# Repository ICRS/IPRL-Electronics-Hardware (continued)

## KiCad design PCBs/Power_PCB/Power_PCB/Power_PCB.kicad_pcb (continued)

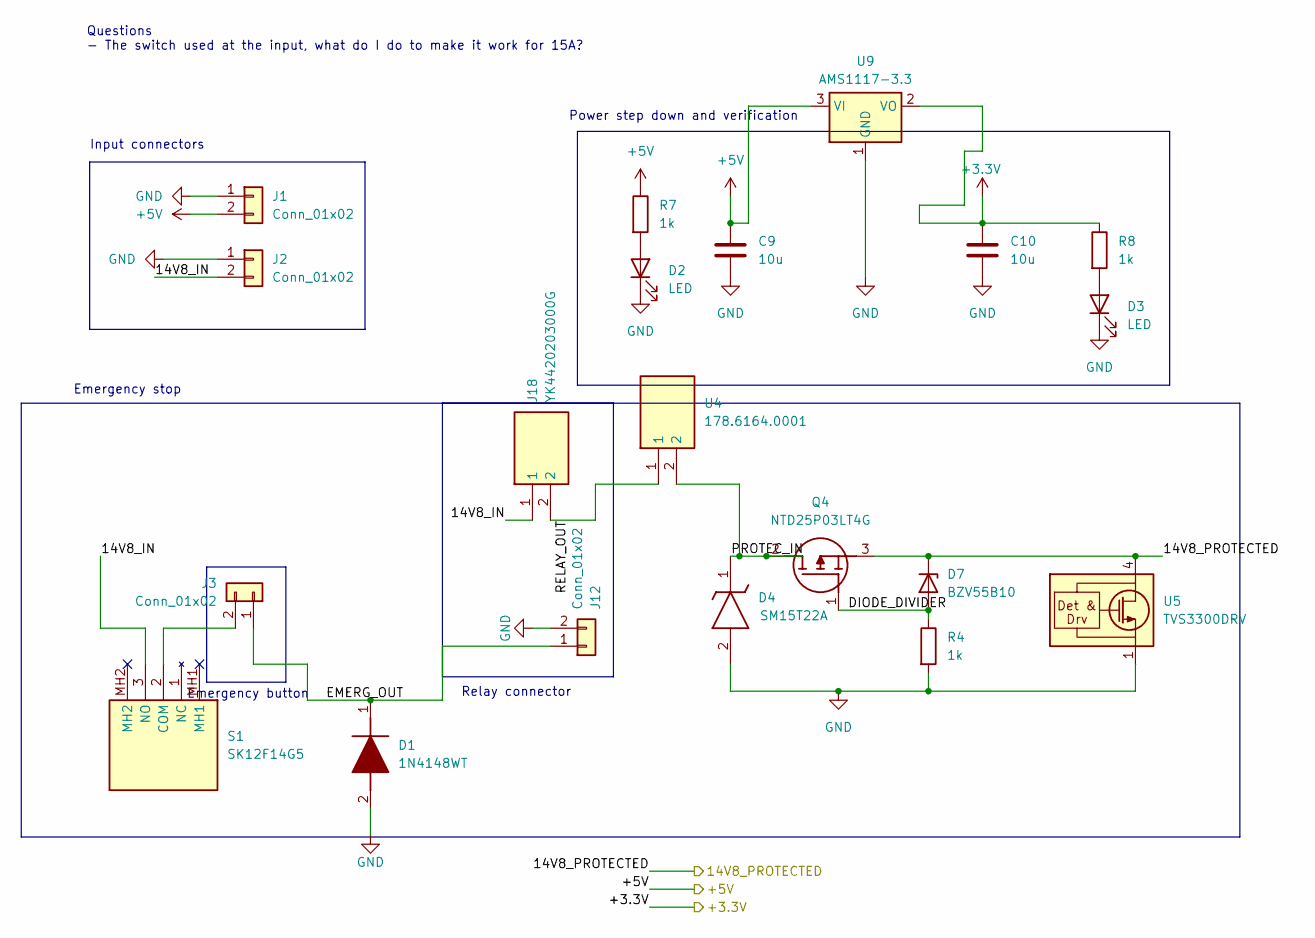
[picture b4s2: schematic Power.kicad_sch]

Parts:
C9, C10: 10u; C_0805_2012Metric
D1: 1N4148WT; SODFL1608X70N; Manufacturer_Part_Number 1N4148WT
D2, D3: LED; LED_0805_2012Metric
D4: SM15T22A; DIOM8059X265N; Manufacturer_Part_Number SM15T22A; Mouser Part Number 511-SM15T22A
D7: BZV55B10; D_MiniMELF
J1, J3, J12: Conn_01x02; TerminalBlock_Altech_AK300-2_P5.00mm
J2: Conn_01x02; AMASS_XT90PW-M_1x02_P10.90mm_Horizontal
J18: YK4420203000G; RHDR2W120P0X950_1X2_2050X1430X1790P; Manufacturer_Part_Number YK4420203000G; Mouser Part Number 649-YK44202030J0G
Q4: NTD25P03LT4G; MJD45H11T4G; Manufacturer_Part_Number NTD25P03LT4G; Mouser Part Number 863-NTD25P03LT4G
R4, R7, R8: 1k; R_0805_2012Metric
S1: SK12F14G5; Manufacturer_Part_Number SK12F14G5; Mouser Part Number 611-SK12F14G5
U4: 178.6164.0001; 178.6164.XXX1; Mouser Part Number 576-178.6164.0001
U5: TVS3300DRV; WSON-6-1EP_2x2mm_P0.65mm_EP1x1.6mm
U9: AMS1117-3.3; SOT-223-3_TabPin2

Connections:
+3.3V: C10.1, R8.1, U9.2 (VO); also elsewhere on the board
+5V: C9.1, J1.2, R7.1, U9.3 (VI); also elsewhere on the board
/14V8_PROTECTED: D7.1 (K), Q4.3 (S), U5.4 (IN), U5.5 (IN), U5.6 (IN); also elsewhere on the board
/Power/14V8_IN: J2.2, J18.1, S1.3 (NO)
/Power/DIODE_DIVIDER: D7.2 (A), Q4.1 (G), R4.1
/Power/EMERG_OUT: D1.1 (K), J3.1, J12.1
/Power/PROTEC_IN: D4.1 (K), Q4.2 (D), U4.2
/Power/RELAY_OUT: J18.2, U4.1
GND: C9.2, C10.2, D1.2 (A), D2.1 (K), D3.1 (K), D4.2 (A), J1.1, J2.1, J12.2, R4.2, U5.1 (GND), U5.2 (GND), U5.3 (GND), U5.7 (GND), U9.1 (GND); also elsewhere on the board
unnamed: D2.2 (A), R7.2
unnamed: D3.2 (A), R8.2
unnamed: J3.2, S1.2 (COM)

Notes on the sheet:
Emergency button
Input connectors
Questions - The switch used at the input, what do I do to make it work for 15A?
Emergency stop
Relay connector
Power step down and verification

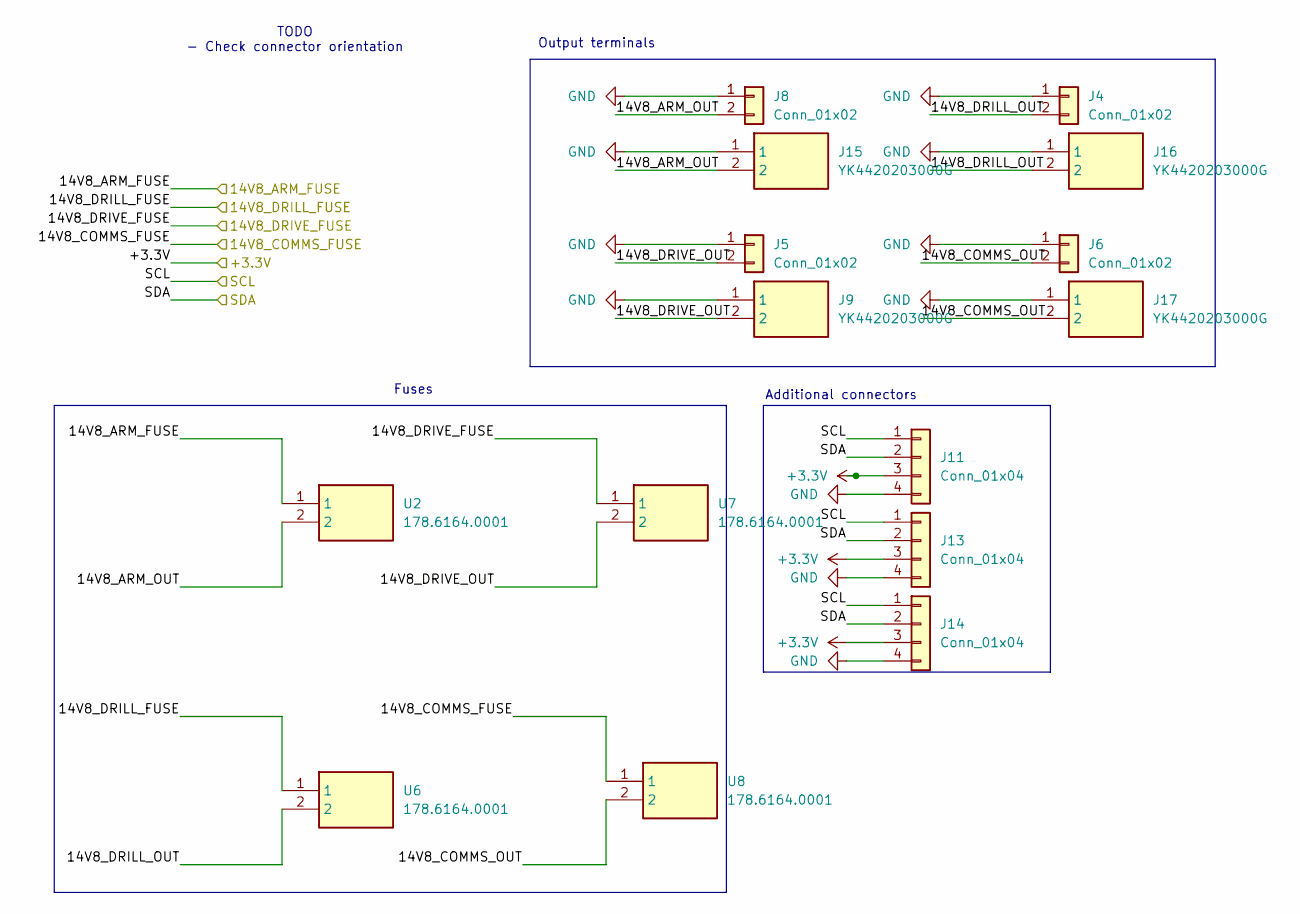
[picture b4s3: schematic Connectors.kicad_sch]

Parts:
J4, J5, J6, J8: Conn_01x02; AMASS_XT60PW-F_1x02_P7.20mm_Horizontal
J9, J15, J16, J17: YK4420203000G; RHDR2W120P0X950_1X2_2050X1430X1790P; Manufacturer_Part_Number YK4420203000G; Mouser Part Number 649-YK44202030J0G
J11, J13, J14: Conn_01x04; JST_PH_S4B-PH-K_1x04_P2.00mm_Horizontal
U2, U6, U7, U8: 178.6164.0001; 178.6164.XXX1; Mouser Part Number 576-178.6164.0001

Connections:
+3.3V: J11.3, J13.3, J14.3; also elsewhere on the board
/14V8_ARM_OUT: U2.1; also elsewhere on the board
/14V8_COMMS_OUT: U8.1; also elsewhere on the board
/14V8_DRILL_OUT: U6.1; also elsewhere on the board
/14V8_DRIVE_OUT: U7.1; also elsewhere on the board
/Connectors/14V8_ARM_OUT: J8.2, J15.2, U2.2
/Connectors/14V8_COMMS_OUT: J6.2, J17.2, U8.2
/Connectors/14V8_DRILL_OUT: J4.2, J16.2, U6.2
/Connectors/14V8_DRIVE_OUT: J5.2, J9.2, U7.2
/SCL: J11.1, J13.1, J14.1; also elsewhere on the board
/SDA: J11.2, J13.2, J14.2; also elsewhere on the board
GND: J4.1, J5.1, J6.1, J8.1, J9.1, J11.4, J13.4, J14.4, J15.1, J16.1, J17.1; also elsewhere on the board

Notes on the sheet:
Additional connectors
Fuses
TODO - Check connector orientation
Output terminals

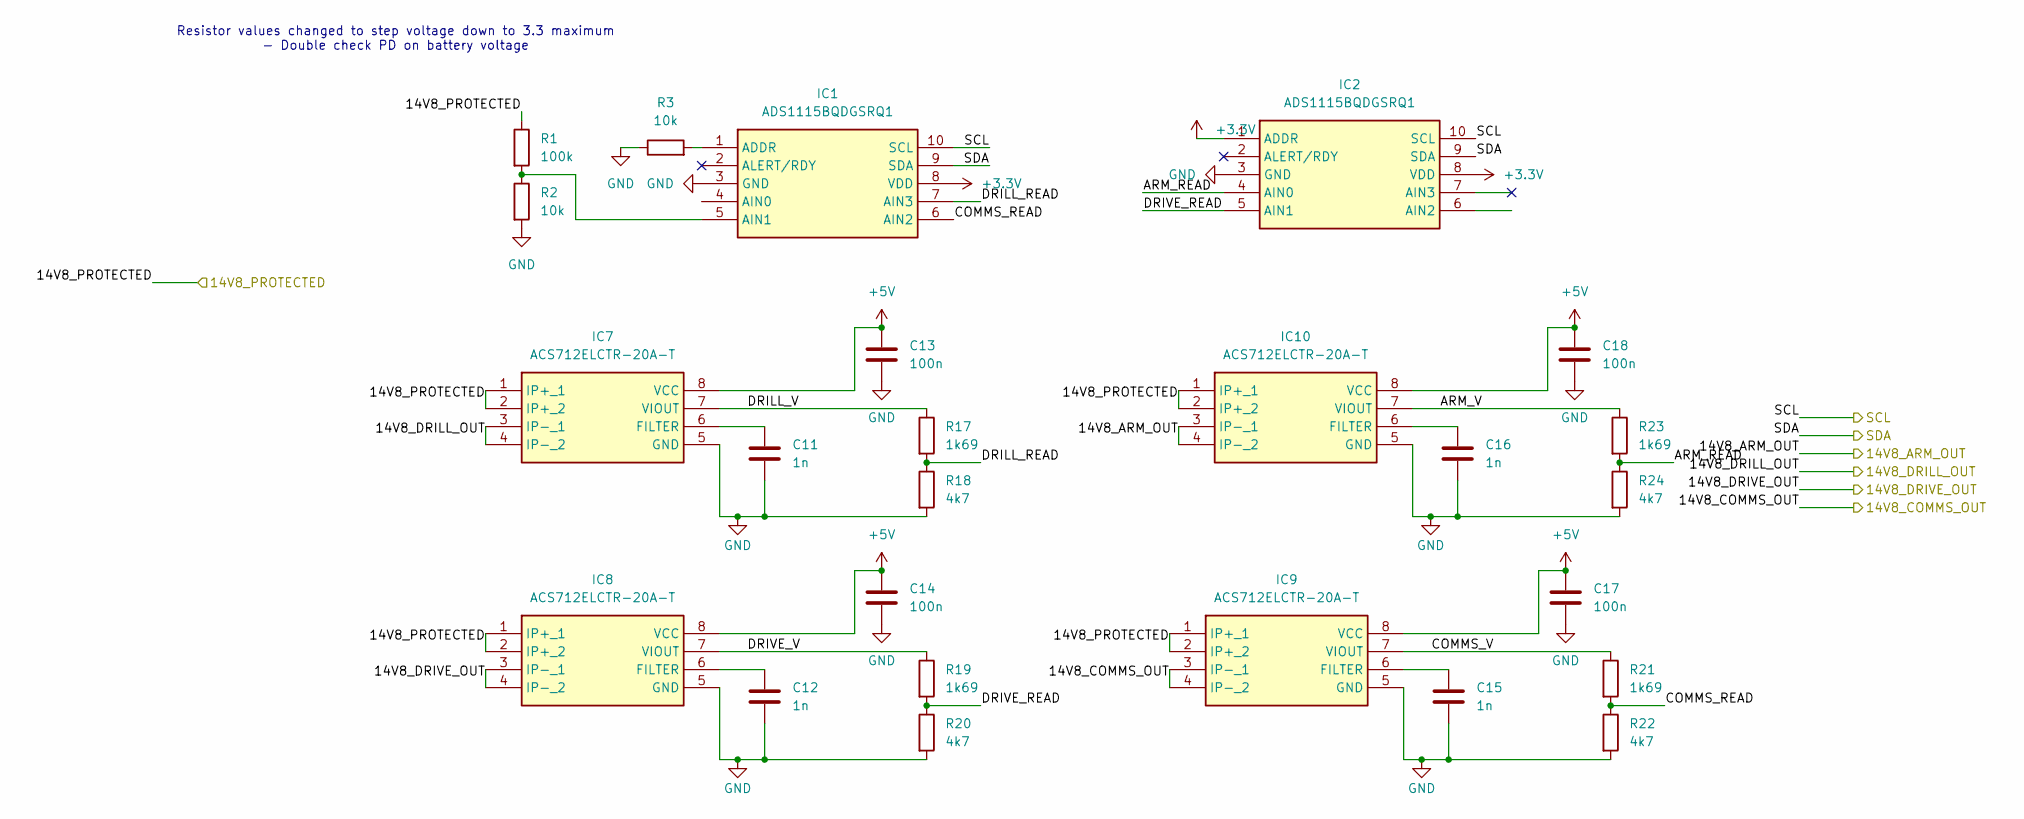
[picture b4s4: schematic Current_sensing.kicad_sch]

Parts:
C11, C12, C15, C16: 1n; C_0805_2012Metric
C13, C14, C17, C18: 100n; C_0805_2012Metric
IC1, IC2: ADS1115BQDGSRQ1; SOP50P490X110-10N; Mouser Part Number 595-ADS1115BQDGSRQ1
IC7, IC8, IC9, IC10: ACS712ELCTR-20A-T; SOIC127P600X175-8N; Manufacturer_Part_Number ACS712ELCTR-20A-T
R1: 100k; R_0805_2012Metric
R2, R3: 10k; R_0805_2012Metric
R17, R19, R21, R23: 1k69; R_0805_2012Metric
R18, R20, R22, R24: 4k7; R_0805_2012Metric

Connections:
+3.3V: IC1.8 (VDD), IC2.1 (ADDR), IC2.8 (VDD); also elsewhere on the board
+5V: C13.1, C14.1, C17.1, C18.1, IC7.8 (VCC), IC8.8 (VCC), IC9.8 (VCC), IC10.8 (VCC); also elsewhere on the board
/14V8_ARM_OUT: IC10.3 (IP-_1), IC10.4 (IP-_2); also elsewhere on the board
/14V8_COMMS_OUT: IC9.3 (IP-_1), IC9.4 (IP-_2); also elsewhere on the board
/14V8_DRILL_OUT: IC7.3 (IP-_1), IC7.4 (IP-_2); also elsewhere on the board
/14V8_DRIVE_OUT: IC8.3 (IP-_1), IC8.4 (IP-_2); also elsewhere on the board
/14V8_PROTECTED: IC7.1 (IP+_1), IC7.2 (IP+_2), IC8.1 (IP+_1), IC8.2 (IP+_2), IC9.1 (IP+_1), IC9.2 (IP+_2), IC10.1 (IP+_1), IC10.2 (IP+_2), R1.1; also elsewhere on the board
/Current_sensing/ARM_READ: IC2.4 (AIN0), R23.2, R24.1
/Current_sensing/ARM_V: IC10.7 (VIOUT), R23.1
/Current_sensing/COMMS_READ: IC1.6 (AIN2), R21.2, R22.1
/Current_sensing/COMMS_V: IC9.7 (VIOUT), R21.1
/Current_sensing/DRILL_READ: IC1.7 (AIN3), R17.2, R18.1
/Current_sensing/DRILL_V: IC7.7 (VIOUT), R17.1
/Current_sensing/DRIVE_READ: IC2.5 (AIN1), R19.2, R20.1
/Current_sensing/DRIVE_V: IC8.7 (VIOUT), R19.1
/SCL: IC1.10 (SCL), IC2.10 (SCL); also elsewhere on the board
/SDA: IC1.9 (SDA), IC2.9 (SDA); also elsewhere on the board
GND: C11.2, C12.2, C13.2, C14.2, C15.2, C16.2, C17.2, C18.2, IC1.3 (GND), IC2.3 (GND), IC7.5 (GND), IC8.5 (GND), IC9.5 (GND), IC10.5 (GND), R2.2, R3.1, R18.2, R20.2, R22.2, R24.2; also elsewhere on the board
unnamed: IC1.1 (ADDR), R3.2
unnamed: IC1.5 (AIN1), R1.2, R2.1
unnamed: C11.1, IC7.6 (FILTER)
unnamed: C12.1, IC8.6 (FILTER)
unnamed: C15.1, IC9.6 (FILTER)
unnamed: C16.1, IC10.6 (FILTER)

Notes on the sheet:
Resistor values changed to step voltage down to 3.3 maximum - Double check PD on battery voltage

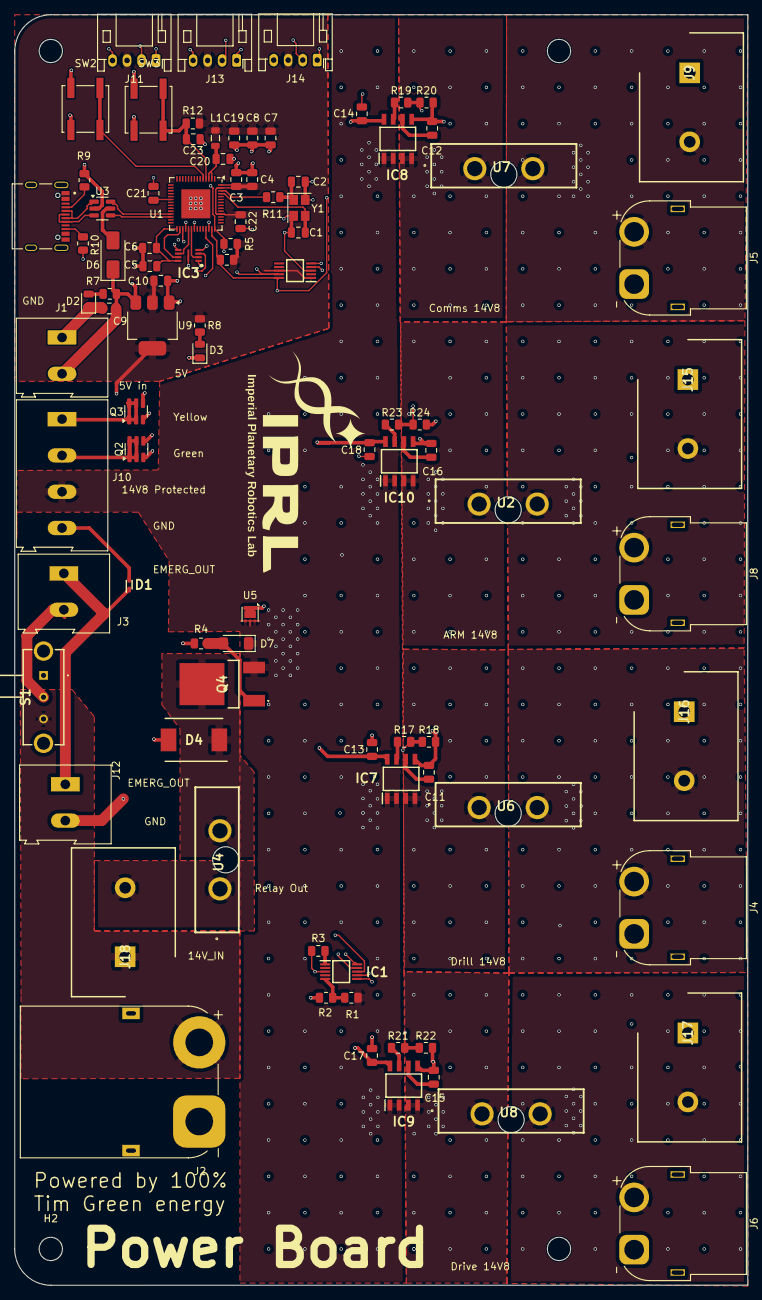
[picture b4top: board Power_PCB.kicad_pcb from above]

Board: 4 copper layers, 101.0 x 175.0 mm, 95 parts (0 on the bottom side), 61 nets.

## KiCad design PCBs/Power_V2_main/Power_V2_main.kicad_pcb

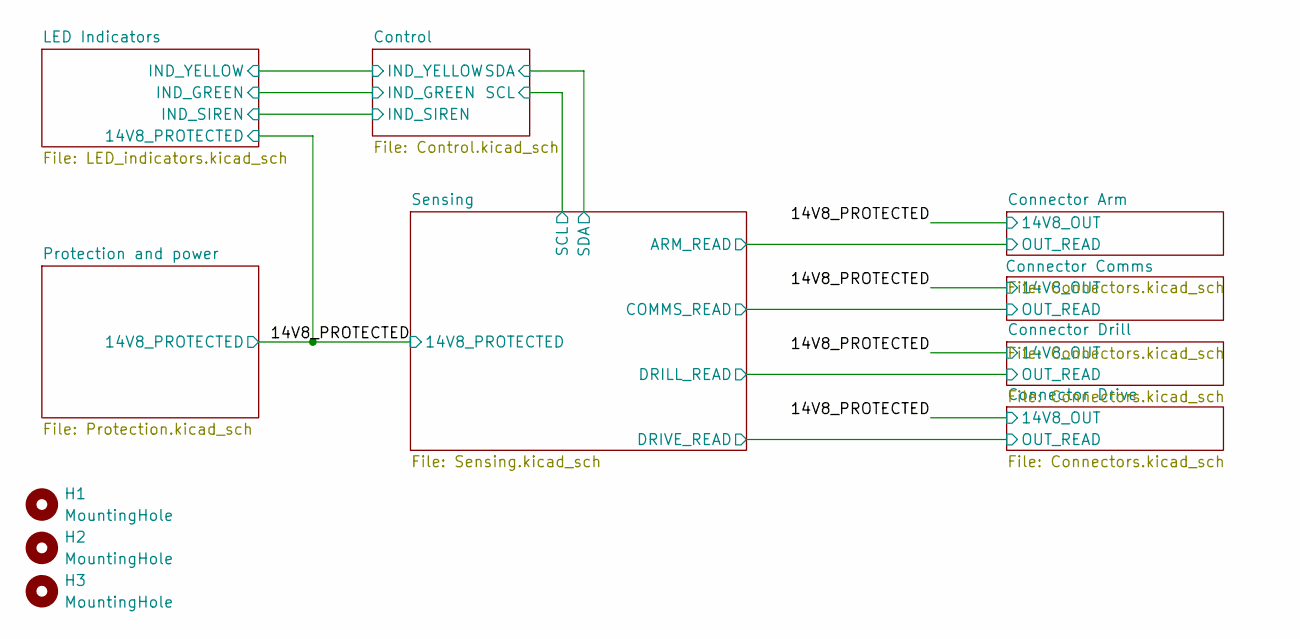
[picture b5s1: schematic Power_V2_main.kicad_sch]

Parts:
H1, H2, H3: MountingHole; MountingHole_2.7mm_M2.5_DIN965_Pad_TopBottom

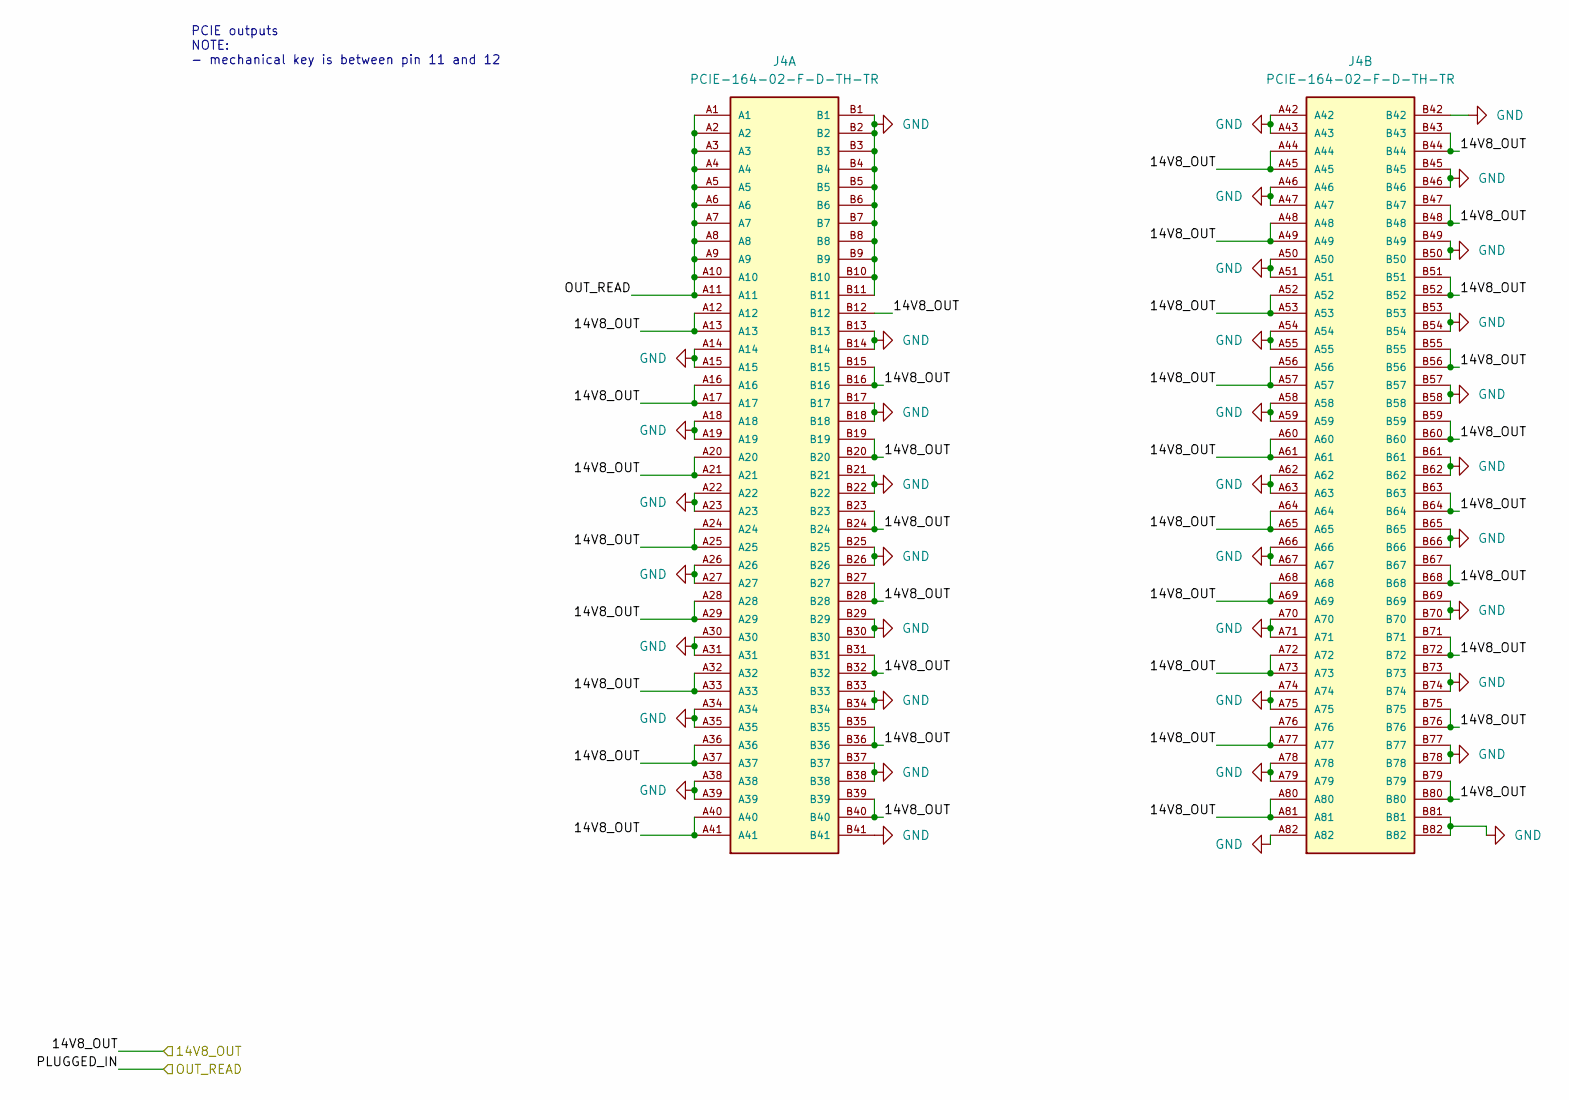
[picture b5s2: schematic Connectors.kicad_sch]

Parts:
J4: PCIE-164-02-F-D-TH-TR; SAMTEC_PCIE-164-02-F-D-TH-TR; PARTREV Y

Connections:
/14V8_PROTECTED: J4.A12, J4.A13, J4.A16, J4.A17, J4.A20, J4.A21, J4.A24, J4.A25, J4.A28, J4.A29, J4.A32, J4.A33, J4.A36, J4.A37, J4.A40, J4.A41, J4.A44, J4.A45, J4.A48, J4.A49, J4.A52, J4.A53, J4.A56, J4.A57, J4.A60, J4.A61, J4.A64, J4.A65, J4.A68, J4.A69, J4.A72, J4.A73, J4.A76, J4.A77, J4.A80, J4.A81, J4.B12, J4.B15, J4.B16, J4.B19, J4.B20, J4.B23, J4.B24, J4.B27, J4.B28, J4.B31, J4.B32, J4.B35, J4.B36, J4.B39, J4.B40, J4.B43, J4.B44, J4.B47, J4.B48, J4.B51, J4.B52, J4.B55, J4.B56, J4.B59, J4.B60, J4.B63, J4.B64, J4.B67, J4.B68, J4.B71, J4.B72, J4.B75, J4.B76, J4.B79, J4.B80; also elsewhere on the board
/Connector Arm/OUT_READ: J4.A1, J4.A2, J4.A3, J4.A4, J4.A5, J4.A6, J4.A7, J4.A8, J4.A9, J4.A10, J4.A11; also elsewhere on the board
GND: J4.A14, J4.A15, J4.A18, J4.A19, J4.A22, J4.A23, J4.A26, J4.A27, J4.A30, J4.A31, J4.A34, J4.A35, J4.A38, J4.A39, J4.A42, J4.A43, J4.A46, J4.A47, J4.A50, J4.A51, J4.A54, J4.A55, J4.A58, J4.A59, J4.A62, J4.A63, J4.A66, J4.A67, J4.A70, J4.A71, J4.A74, J4.A75, J4.A78, J4.A79, J4.A82, J4.B1, J4.B2, J4.B3, J4.B4, J4.B5, J4.B6, J4.B7, J4.B8, J4.B9, J4.B10, J4.B11, J4.B13, J4.B14, J4.B17, J4.B18, J4.B21, J4.B22, J4.B25, J4.B26, J4.B29, J4.B30, J4.B33, J4.B34, J4.B37, J4.B38, J4.B41, J4.B42, J4.B45, J4.B46, J4.B49, J4.B50, J4.B53, J4.B54, J4.B57, J4.B58, J4.B61, J4.B62, J4.B65, J4.B66, J4.B69, J4.B70, J4.B73, J4.B74, J4.B77, J4.B78, J4.B81, J4.B82; also elsewhere on the board

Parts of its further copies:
J5, J6, J8: PCIE-164-02-F-D-TH-TR; SAMTEC_PCIE-164-02-F-D-TH-TR; PARTREV Y

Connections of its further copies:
/14V8_PROTECTED: J5.A12, J5.A13, J5.A16, J5.A17, J5.A20, J5.A21, J5.A24, J5.A25, J5.A28, J5.A29, J5.A32, J5.A33, J5.A36, J5.A37, J5.A40, J5.A41, J5.A44, J5.A45, J5.A48, J5.A49, J5.A52, J5.A53, J5.A56, J5.A57, J5.A60, J5.A61, J5.A64, J5.A65, J5.A68, J5.A69, J5.A72, J5.A73, J5.A76, J5.A77, J5.A80, J5.A81, J5.B12, J5.B15, J5.B16, J5.B19, J5.B20, J5.B23, J5.B24, J5.B27, J5.B28, J5.B31, J5.B32, J5.B35, J5.B36, J5.B39, J5.B40, J5.B43, J5.B44, J5.B47, J5.B48, J5.B51, J5.B52, J5.B55, J5.B56, J5.B59, J5.B60, J5.B63, J5.B64, J5.B67, J5.B68, J5.B71, J5.B72, J5.B75, J5.B76, J5.B79, J5.B80, J6.A12, J6.A13, J6.A16, J6.A17, J6.A20, J6.A21, J6.A24, J6.A25, J6.A28, J6.A29, J6.A32, J6.A33, J6.A36, J6.A37, J6.A40, J6.A41, J6.A44, J6.A45, J6.A48, J6.A49, J6.A52, J6.A53, J6.A56, J6.A57, J6.A60, J6.A61, J6.A64, J6.A65, J6.A68, J6.A69, J6.A72, J6.A73, J6.A76, J6.A77, J6.A80, J6.A81, J6.B12, J6.B15, J6.B16, J6.B19, J6.B20, J6.B23, J6.B24, J6.B27, J6.B28, J6.B31, J6.B32, J6.B35, J6.B36, J6.B39, J6.B40, J6.B43, J6.B44, J6.B47, J6.B48, J6.B51, J6.B52, J6.B55, J6.B56, J6.B59, J6.B60, J6.B63, J6.B64, J6.B67, J6.B68, J6.B71, J6.B72, J6.B75, J6.B76, J6.B79, J6.B80, J8.A12, J8.A13, J8.A16, J8.A17, J8.A20, J8.A21, J8.A24, J8.A25, J8.A28, J8.A29, J8.A32, J8.A33, J8.A36, J8.A37, J8.A40, J8.A41, J8.A44, J8.A45, J8.A48, J8.A49, J8.A52, J8.A53, J8.A56, J8.A57, J8.A60, J8.A61, J8.A64, J8.A65, J8.A68, J8.A69, J8.A72, J8.A73, J8.A76, J8.A77, J8.A80, J8.A81, J8.B12, J8.B15, J8.B16, J8.B19, J8.B20, J8.B23, J8.B24, J8.B27, J8.B28, J8.B31, J8.B32, J8.B35, J8.B36, J8.B39, J8.B40, J8.B43, J8.B44, J8.B47, J8.B48, J8.B51, J8.B52, J8.B55, J8.B56, J8.B59, J8.B60, J8.B63, J8.B64, J8.B67, J8.B68, J8.B71, J8.B72, J8.B75, J8.B76, J8.B79, J8.B80; also elsewhere on the board
/Connector Comms/OUT_READ: J5.A1, J5.A2, J5.A3, J5.A4, J5.A5, J5.A6, J5.A7, J5.A8, J5.A9, J5.A10, J5.A11; also elsewhere on the board
/Connector Drill/OUT_READ: J8.A1, J8.A2, J8.A3, J8.A4, J8.A5, J8.A6, J8.A7, J8.A8, J8.A9, J8.A10, J8.A11; also elsewhere on the board
/Connector Drive/OUT_READ: J6.A1, J6.A2, J6.A3, J6.A4, J6.A5, J6.A6, J6.A7, J6.A8, J6.A9, J6.A10, J6.A11; also elsewhere on the board
GND: J5.A14, J5.A15, J5.A18, J5.A19, J5.A22, J5.A23, J5.A26, J5.A27, J5.A30, J5.A31, J5.A34, J5.A35, J5.A38, J5.A39, J5.A42, J5.A43, J5.A46, J5.A47, J5.A50, J5.A51, J5.A54, J5.A55, J5.A58, J5.A59, J5.A62, J5.A63, J5.A66, J5.A67, J5.A70, J5.A71, J5.A74, J5.A75, J5.A78, J5.A79, J5.A82, J5.B1, J5.B2, J5.B3, J5.B4, J5.B5, J5.B6, J5.B7, J5.B8, J5.B9, J5.B10, J5.B11, J5.B13, J5.B14, J5.B17, J5.B18, J5.B21, J5.B22, J5.B25, J5.B26, J5.B29, J5.B30, J5.B33, J5.B34, J5.B37, J5.B38, J5.B41, J5.B42, J5.B45, J5.B46, J5.B49, J5.B50, J5.B53, J5.B54, J5.B57, J5.B58, J5.B61, J5.B62, J5.B65, J5.B66, J5.B69, J5.B70, J5.B73, J5.B74, J5.B77, J5.B78, J5.B81, J5.B82, J6.A14, J6.A15, J6.A18, J6.A19, J6.A22, J6.A23, J6.A26, J6.A27, J6.A30, J6.A31, J6.A34, J6.A35, J6.A38, J6.A39, J6.A42, J6.A43, J6.A46, J6.A47, J6.A50, J6.A51, J6.A54, J6.A55, J6.A58, J6.A59, J6.A62, J6.A63, J6.A66, J6.A67, J6.A70, J6.A71, J6.A74, J6.A75, J6.A78, J6.A79, J6.A82, J6.B1, J6.B2, J6.B3, J6.B4, J6.B5, J6.B6, J6.B7, J6.B8, J6.B9, J6.B10, J6.B11, J6.B13, J6.B14, J6.B17, J6.B18, J6.B21, J6.B22, J6.B25, J6.B26, J6.B29, J6.B30, J6.B33, J6.B34, J6.B37, J6.B38, J6.B41, J6.B42, J6.B45, J6.B46, J6.B49, J6.B50, J6.B53, J6.B54, J6.B57, J6.B58, J6.B61, J6.B62, J6.B65, J6.B66, J6.B69, J6.B70, J6.B73, J6.B74, J6.B77, J6.B78, J6.B81, J6.B82, J8.A14, J8.A15, J8.A18, J8.A19, J8.A22, J8.A23, J8.A26, J8.A27, J8.A30, J8.A31, J8.A34, J8.A35, J8.A38, J8.A39, J8.A42, J8.A43, J8.A46, J8.A47, J8.A50, J8.A51, J8.A54, J8.A55, J8.A58, J8.A59, J8.A62, J8.A63, J8.A66, J8.A67, J8.A70, J8.A71, J8.A74, J8.A75, J8.A78, J8.A79, J8.A82, J8.B1, J8.B2, J8.B3, J8.B4, J8.B5, J8.B6, J8.B7, J8.B8, J8.B9, J8.B10, J8.B11, J8.B13, J8.B14, J8.B17, J8.B18, J8.B21, J8.B22, J8.B25, J8.B26, J8.B29, J8.B30, J8.B33, J8.B34, J8.B37, J8.B38, J8.B41, J8.B42, J8.B45, J8.B46, J8.B49, J8.B50, J8.B53, J8.B54, J8.B57, J8.B58, J8.B61, J8.B62, J8.B65, J8.B66, J8.B69, J8.B70, J8.B73, J8.B74, J8.B77, J8.B78, J8.B81, J8.B82; also elsewhere on the board

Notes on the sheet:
PCIE outputs NOTE: - mechanical key is between pin 11 and 12

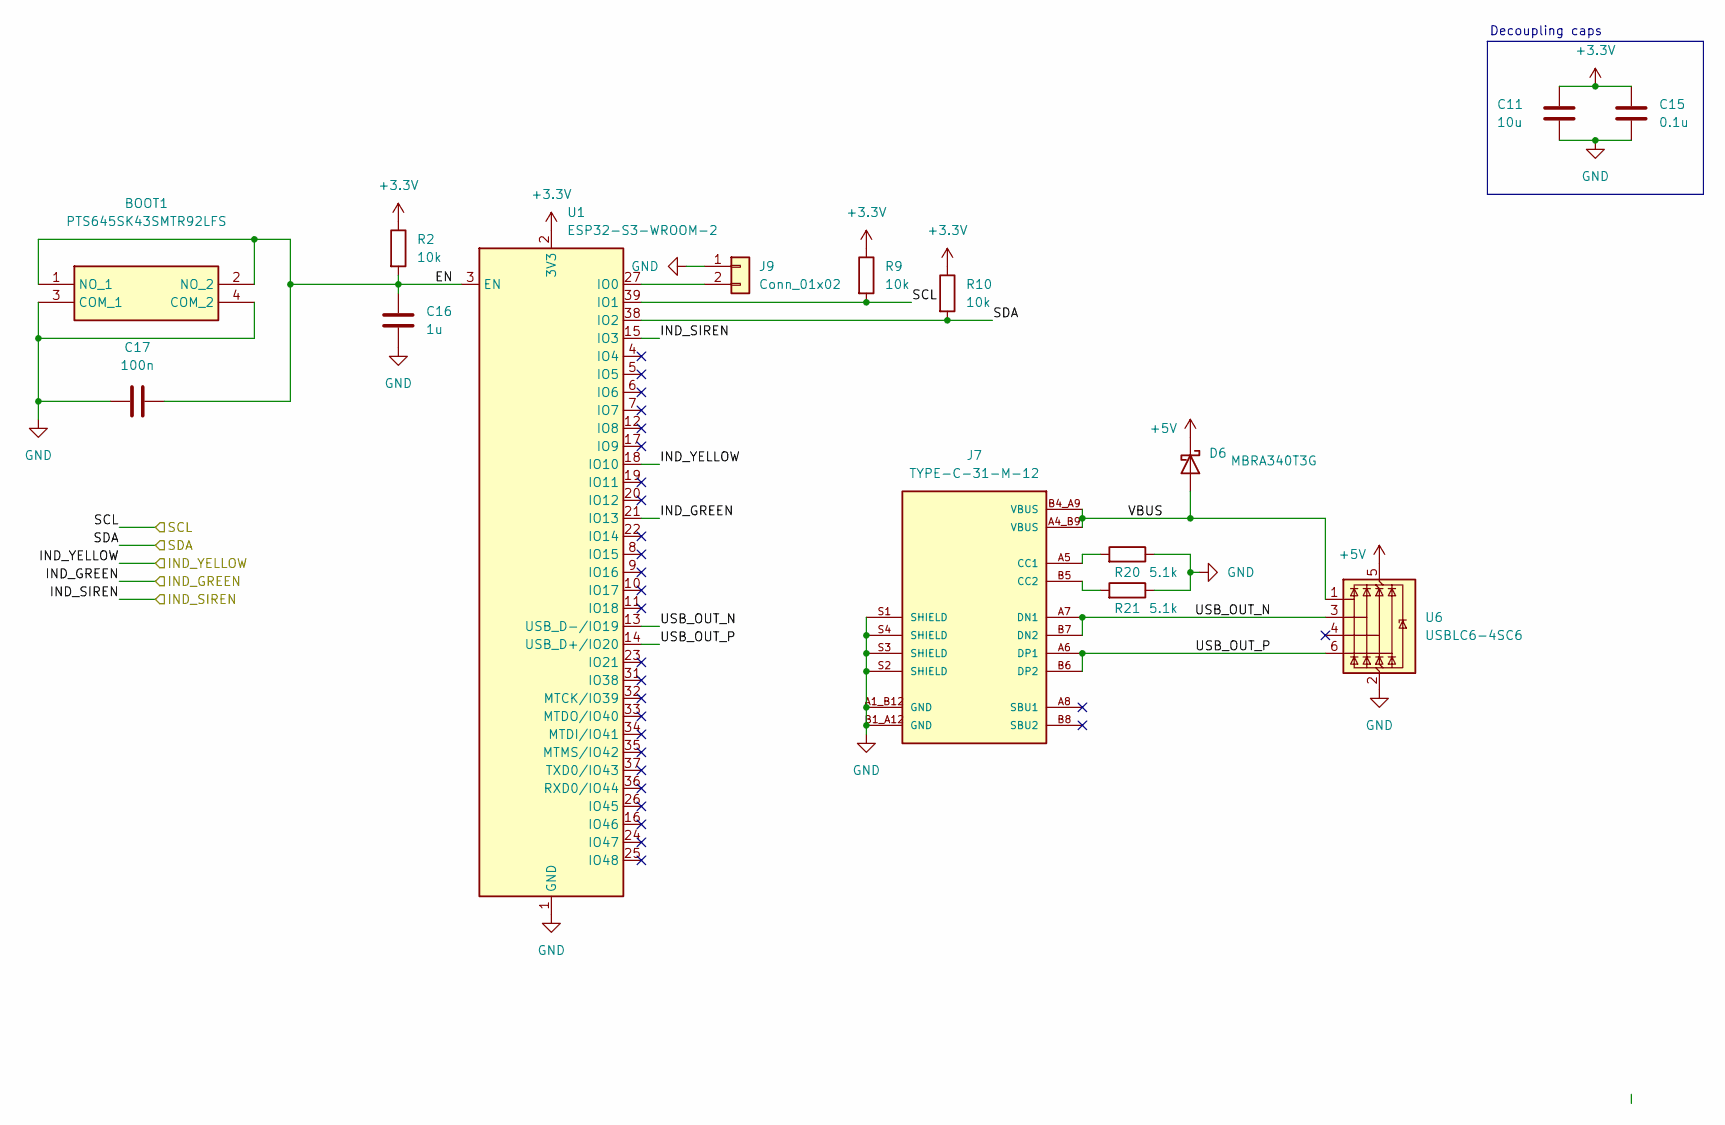
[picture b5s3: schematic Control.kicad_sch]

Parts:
BOOT1: PTS645SK43SMTR92LFS; Manufacturer_Part_Number PTS645SK43SMTR92LFS; Mouser Part Number 611-PTS645SK43SMTR92
C11: 10u; C_0805_2012Metric
C15: 0.1u; C_0805_2012Metric
C16: 1u; C_0805_2012Metric
C17: 100n; C_0805_2012Metric
D6: MBRA340T3G; D_SMA
J7: TYPE-C-31-M-12; PARTREV 2020.12.08
J9: Conn_01x02; PinHeader_1x02_P2.54mm_Vertical
R2, R9, R10: 10k; R_0805_2012Metric
R20, R21: 5.1k; R_0805_2012Metric
U1: ESP32-S3-WROOM-2
U6: USBLC6-4SC6; SOT-23-6

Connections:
+3.3V: C11.1, C15.1, R2.1, R9.1, R10.1, U1.2 (3V3); also elsewhere on the board
+5V: D6.1 (K), U6.5 (VBUS); also elsewhere on the board
/Control/EN: BOOT1.1 (NO_1), BOOT1.2 (NO_2), C16.1, C17.2, R2.2, U1.3 (EN)
/Control/IND_GREEN: U1.21 (IO13); also elsewhere on the board
/Control/IND_SIREN: U1.15 (IO3); also elsewhere on the board
/Control/IND_YELLOW: U1.18 (IO10); also elsewhere on the board
/Control/SCL: R9.2, U1.39 (IO1); also elsewhere on the board
/Control/SDA: R10.2, U1.38 (IO2); also elsewhere on the board
/Control/USB_OUT_N: J7.A7 (DN1), J7.B7 (DN2), U1.13 (USB_D-/IO19), U6.3 (I/O2)
/Control/USB_OUT_P: J7.A6 (DP1), J7.B6 (DP2), U1.14 (USB_D+/IO20), U6.6 (I/O4)
/Control/VBUS: D6.2 (A), J7.A4_B9 (VBUS), J7.B4_A9 (VBUS), U6.1 (I/O1)
GND: BOOT1.3 (COM_1), BOOT1.4 (COM_2), C11.2, C15.2, C16.2, C17.1, J7.A1_B12 (GND), J7.B1_A12 (GND), J7.S1 (SHIELD), J7.S2 (SHIELD), J7.S3 (SHIELD), J7.S4 (SHIELD), J9.1, R20.1, R21.1, U1.1 (GND), U1.40 (GND), U1.41 (GND), U6.2 (GND); also elsewhere on the board
unnamed: J7.A5 (CC1), R20.2
unnamed: J7.B5 (CC2), R21.2
unnamed: J9.2, U1.27 (IO0)

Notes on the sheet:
Decoupling caps

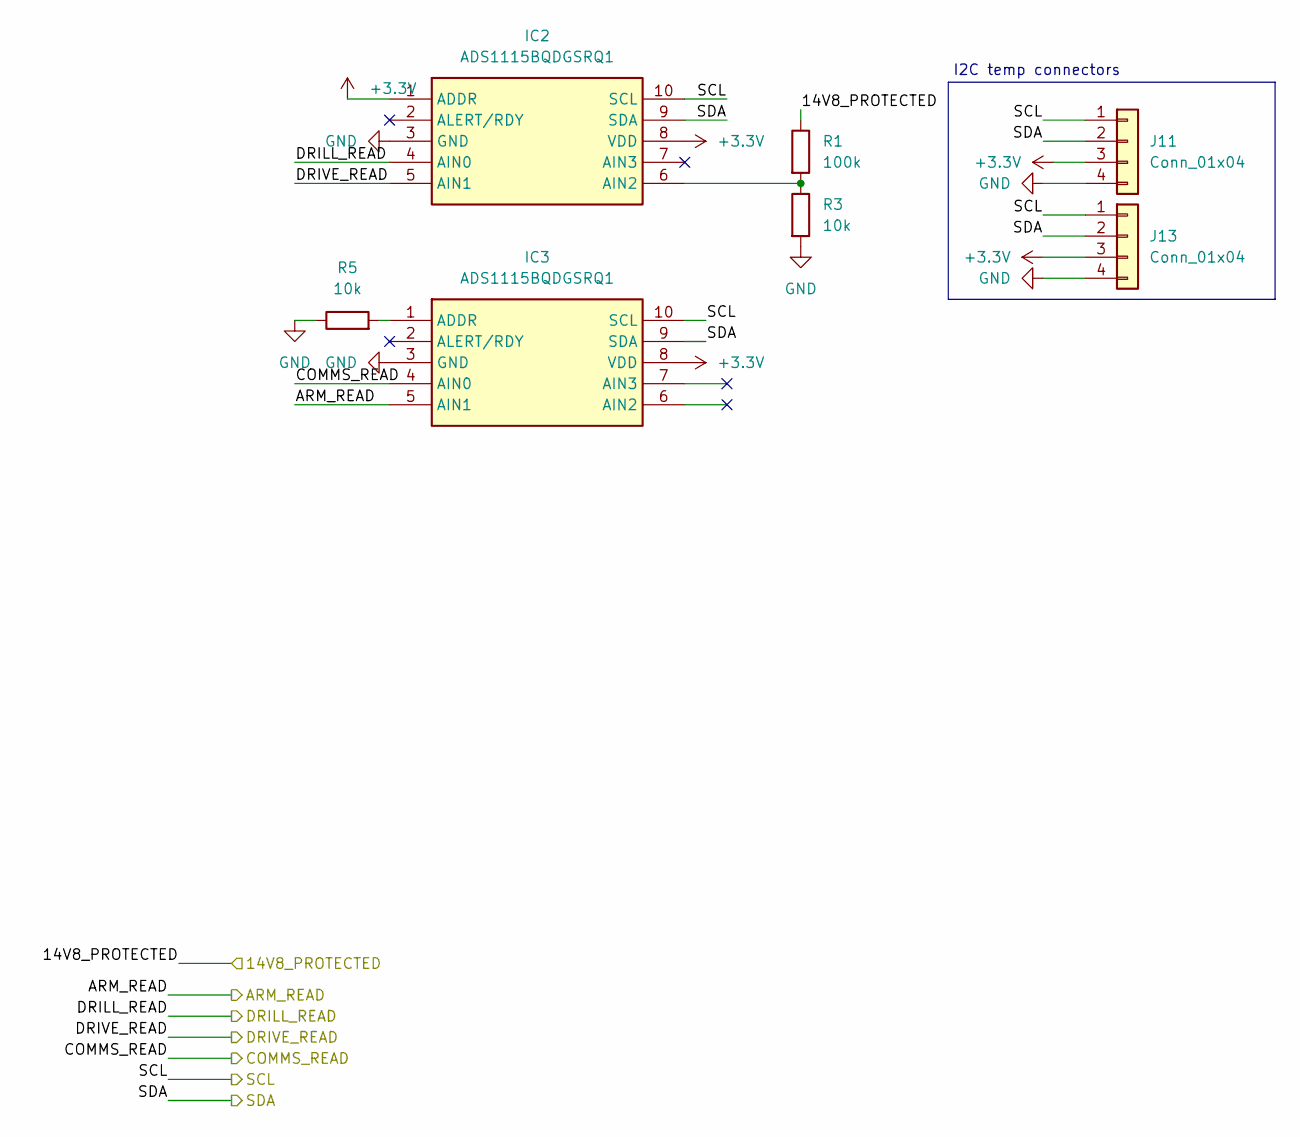
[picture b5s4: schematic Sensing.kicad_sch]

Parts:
IC2, IC3: ADS1115BQDGSRQ1; SOP50P490X110-10N; Mouser Part Number 595-ADS1115BQDGSRQ1
J11, J13: Conn_01x04; JST_GH_SM04B-GHS-TB_1x04-1MP_P1.25mm_Horizontal
R1: 100k; R_0805_2012Metric
R3, R5: 10k; R_0805_2012Metric

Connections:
+3.3V: IC2.1 (ADDR), IC2.8 (VDD), IC3.8 (VDD), J11.3, J13.3; also elsewhere on the board
/14V8_PROTECTED: R1.1; also elsewhere on the board
/Connector Arm/OUT_READ: IC3.5 (AIN1); also elsewhere on the board
/Connector Comms/OUT_READ: IC3.4 (AIN0); also elsewhere on the board
/Connector Drill/OUT_READ: IC2.4 (AIN0); also elsewhere on the board
/Connector Drive/OUT_READ: IC2.5 (AIN1); also elsewhere on the board
/Control/SCL: IC2.10 (SCL), IC3.10 (SCL), J11.1, J13.1; also elsewhere on the board
/Control/SDA: IC2.9 (SDA), IC3.9 (SDA), J11.2, J13.2; also elsewhere on the board
GND: IC2.3 (GND), IC3.3 (GND), J11.4, J13.4, R3.2, R5.1; also elsewhere on the board
unnamed: IC2.6 (AIN2), R1.2, R3.1
unnamed: IC3.1 (ADDR), R5.2

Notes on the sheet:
I2C temp connectors

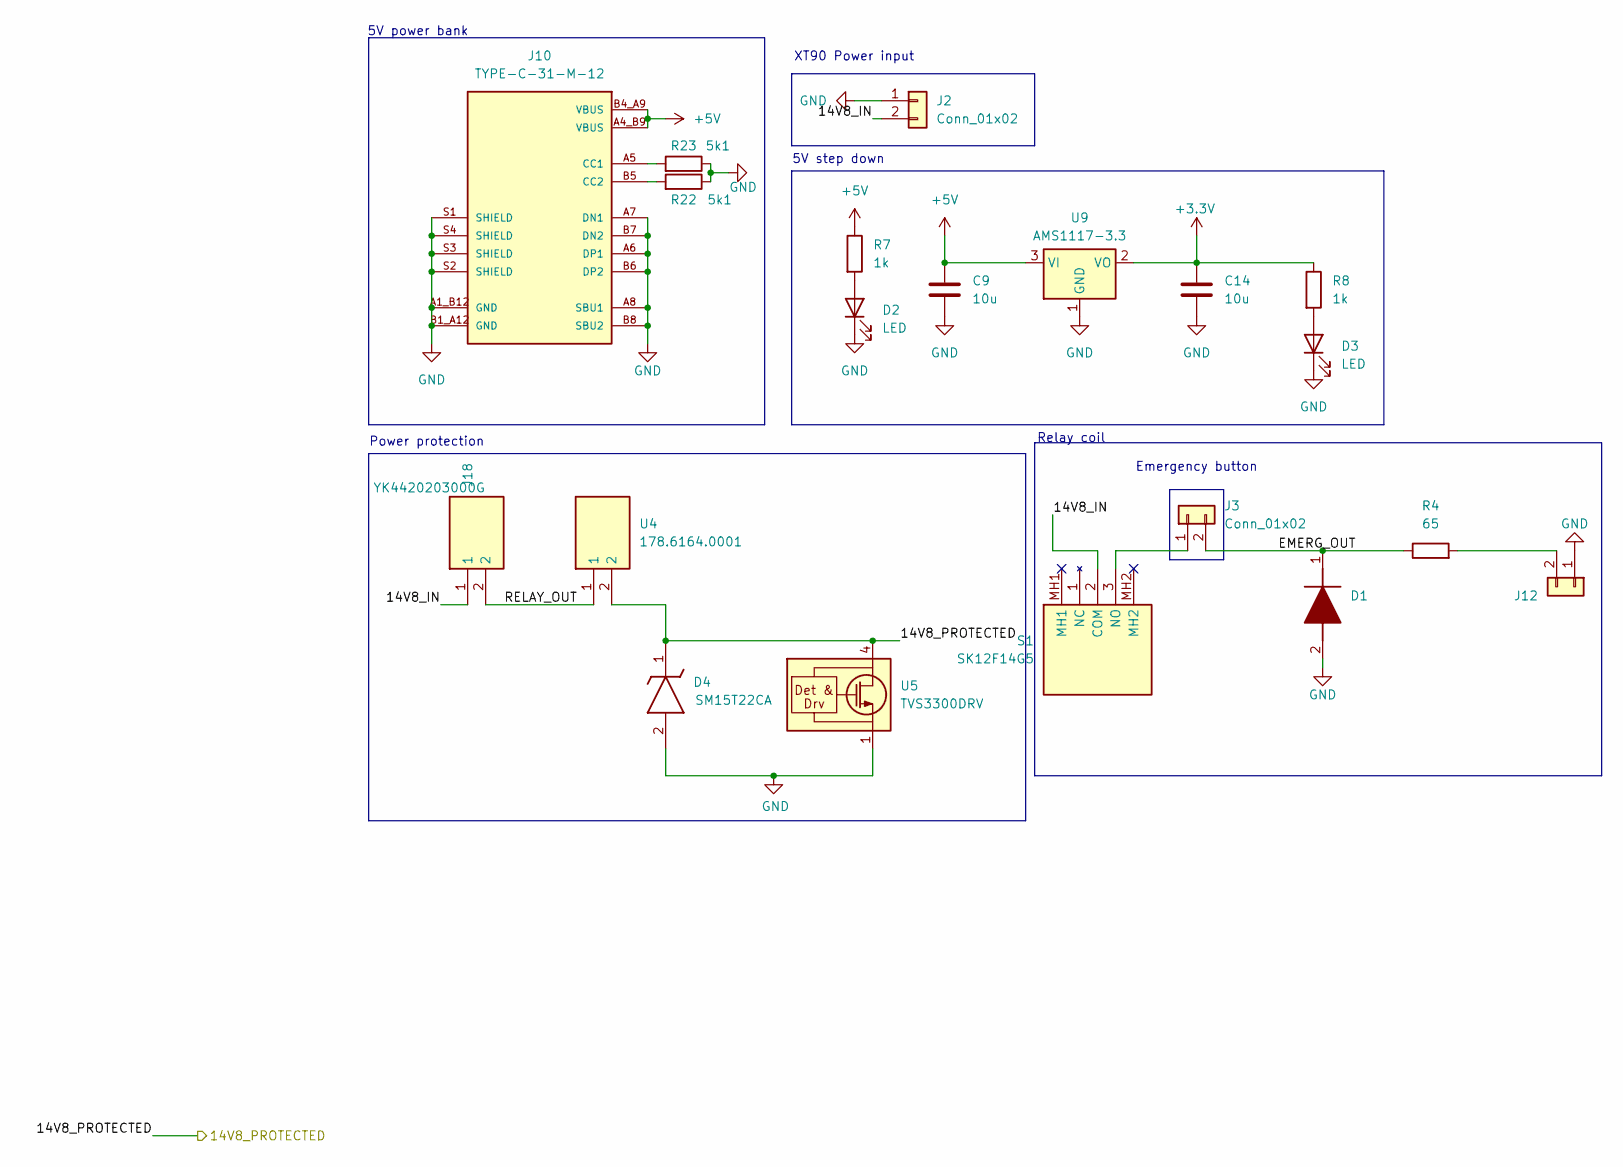
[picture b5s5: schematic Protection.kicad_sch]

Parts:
C9, C14: 10u; C_0805_2012Metric
D1: 1N4148WT; SODFL1608X70N; Manufacturer_Part_Number 1N4148WT
D2, D3: LED; LED_0805_2012Metric
D4: SM15T22CA; DIOM8059X265N; Manufacturer_Part_Number SM15T22A; Mouser Part Number 511-SM15T22A
J2: Conn_01x02; AMASS_XT90PW-M_1x02_P10.90mm_Horizontal
J3, J12: Conn_01x02; TerminalBlock_Altech_AK300-2_P5.00mm
J10: TYPE-C-31-M-12; PARTREV 2020.12.08
J18: YK4420203000G; RHDR2W120P0X950_1X2_2050X1430X1790P; Manufacturer_Part_Number YK4420203000G; Mouser Part Number 649-YK44202030J0G
R4: 65; R_Axial_DIN0414_L11.9mm_D4.5mm_P15.24mm_Horizontal
R7, R8: 1k; R_0805_2012Metric
R22, R23: 5k1; R_0805_2012Metric
S1: SK12F14G5; Manufacturer_Part_Number SK12F14G5; Mouser Part Number 611-SK12F14G5
U4: 178.6164.0001; 178.6164.XXX1; Mouser Part Number 576-178.6164.0001
U5: TVS3300DRV; WSON-6-1EP_2x2mm_P0.65mm_EP1x1.6mm
U9: AMS1117-3.3; SOT-223-3_TabPin2

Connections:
+3.3V: C14.1, R8.1, U9.2 (VO); also elsewhere on the board
+5V: C9.1, J10.A4_B9 (VBUS), J10.B4_A9 (VBUS), R7.1, U9.3 (VI); also elsewhere on the board
/14V8_PROTECTED: D4.1 (K), U4.2, U5.4 (IN), U5.5 (IN), U5.6 (IN); also elsewhere on the board
/Protection and power/14V8_IN: J2.2, J18.1, S1.2 (COM)
/Protection and power/EMERG_OUT: D1.1 (K), J3.2, R4.1
/Protection and power/RELAY_OUT: J18.2, U4.1
GND: C9.2, C14.2, D1.2 (A), D2.1 (K), D3.1 (K), D4.2 (A), J2.1, J10.A1_B12 (GND), J10.A6 (DP1), J10.A7 (DN1), J10.A8 (SBU1), J10.B1_A12 (GND), J10.B6 (DP2), J10.B7 (DN2), J10.B8 (SBU2), J10.S1 (SHIELD), J10.S2 (SHIELD), J10.S3 (SHIELD), J10.S4 (SHIELD), J12.1, R22.1, R23.1, U5.1 (GND), U5.2 (GND), U5.3 (GND), U5.7 (GND), U9.1 (GND); also elsewhere on the board
unnamed: D2.2 (A), R7.2
unnamed: D3.2 (A), R8.2
unnamed: J3.1, S1.3 (NO)
unnamed: J10.A5 (CC1), R23.2
unnamed: J10.B5 (CC2), R22.2
unnamed: J12.2, R4.2

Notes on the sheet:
5V step down
XT90 Power input
5V power bank
Emergency button
Power protection
Relay coil

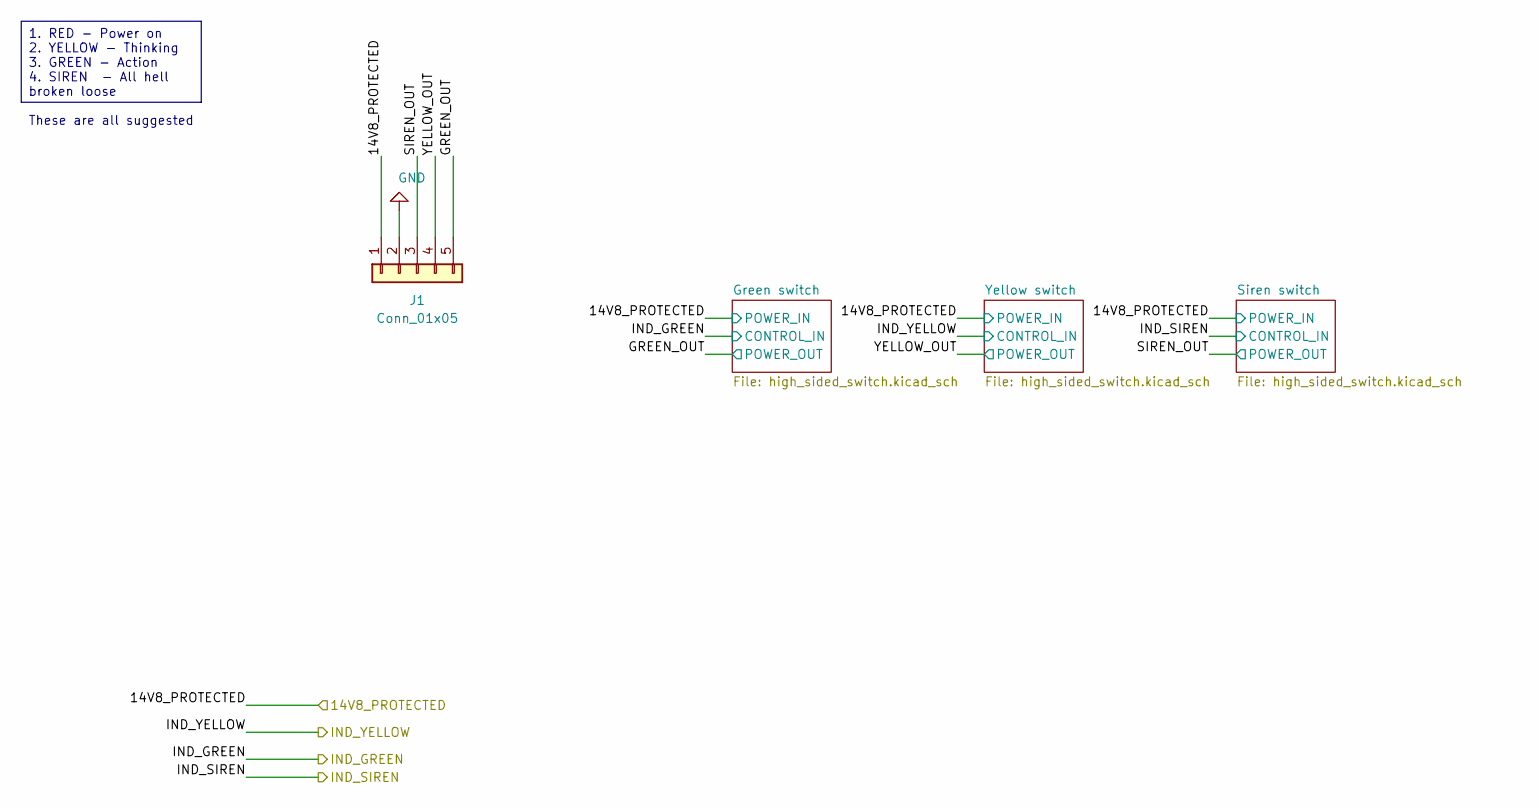
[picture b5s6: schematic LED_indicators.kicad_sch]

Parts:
J1: Conn_01x05; JST_EH_B5B-EH-A_1x05_P2.50mm_Vertical

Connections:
/14V8_PROTECTED: J1.1; also elsewhere on the board
/LED Indicators/GREEN_OUT: J1.3; also elsewhere on the board
/LED Indicators/YELLOW_OUT: J1.4; also elsewhere on the board
GND: J1.2; also elsewhere on the board

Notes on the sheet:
1. RED - Power on 2. YELLOW - Thinking 3. GREEN - Action 4. SIREN - All hell broken loose These are all suggested
